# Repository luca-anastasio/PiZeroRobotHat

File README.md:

# PiZeroRobotHat
Raspberry Pi Zero Robot Hat

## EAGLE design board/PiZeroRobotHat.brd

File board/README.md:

## Pi Zero Robot Hat

### top

### bottom

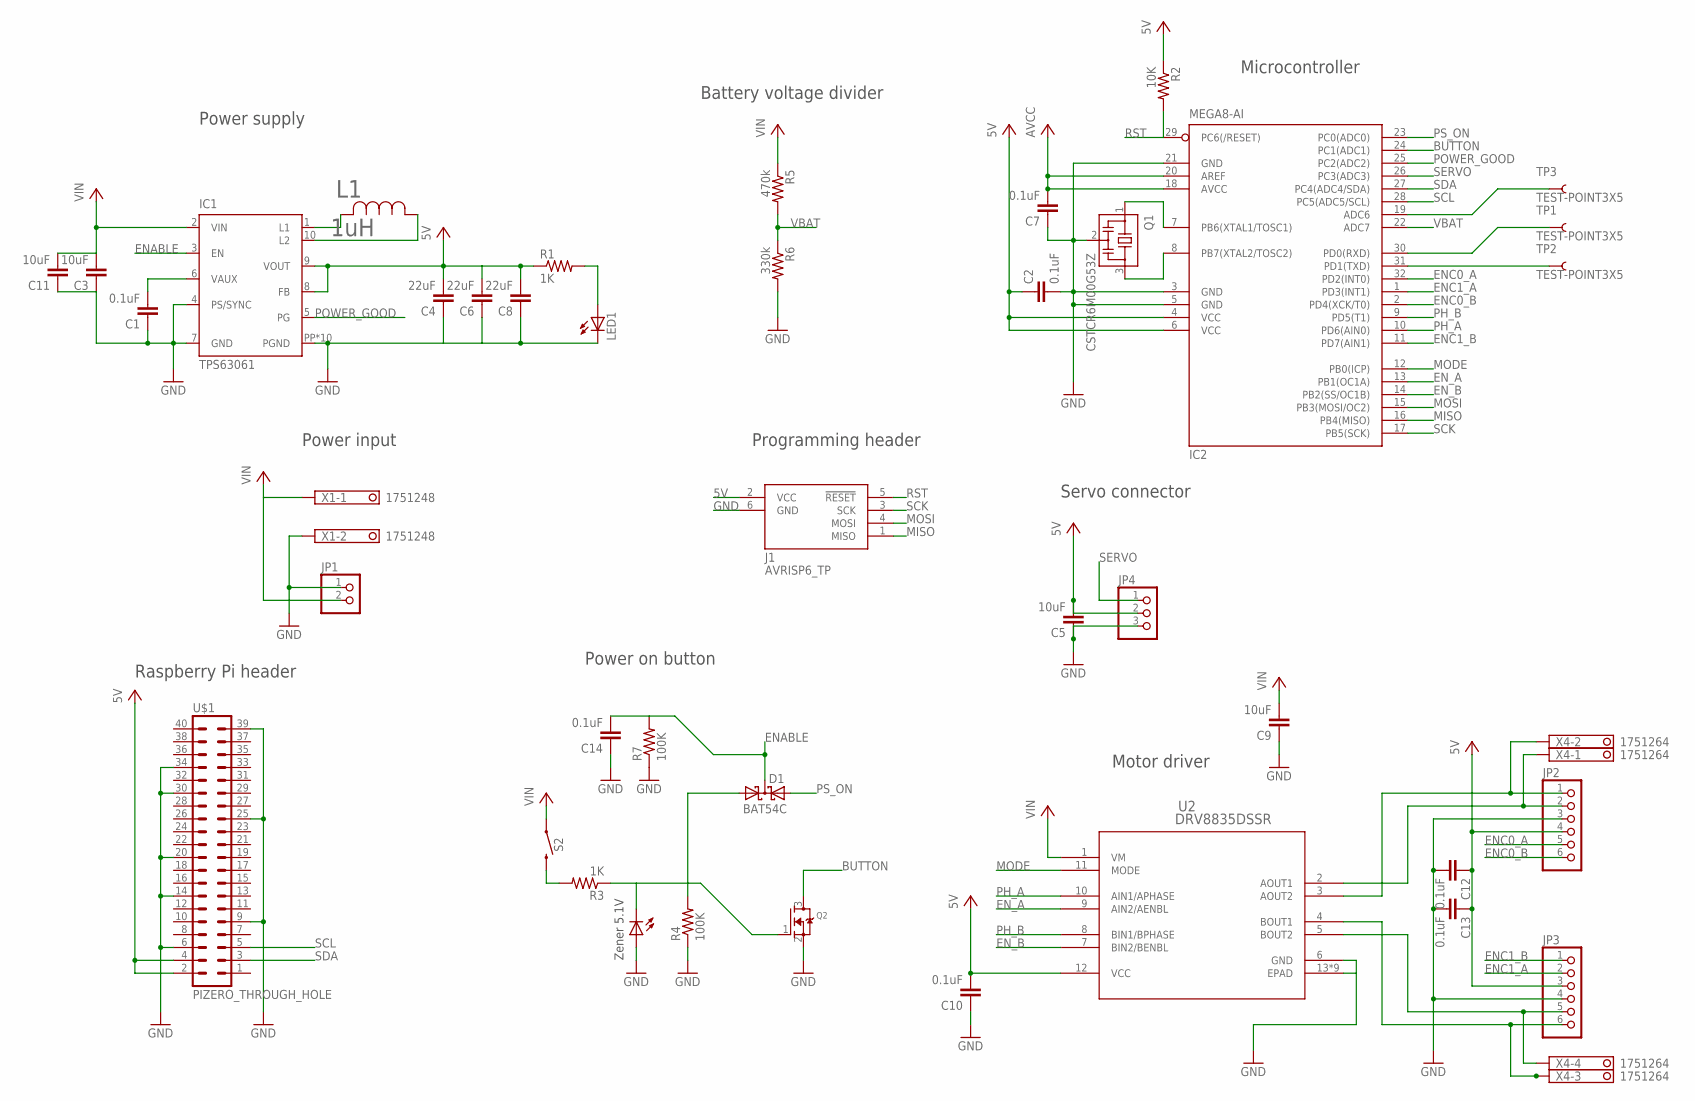
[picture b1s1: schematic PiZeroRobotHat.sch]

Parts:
C1, C2, C7, C10, C12, C13, C14: 0.1uF; C0603K
C3, C5, C9, C11: 10uF; C0805K
C4, C6, C8: 22uF; C0805K
D1: BAT54C; SOT23
IC1: TPS63061; DSC-S-PWSON-N10
IC2: MEGA8-AI; TQFP32-08
J1: AVRISP6_TP; 2X3_TP
JP1: PINHD-1X2; 1X02
JP2, JP3: PINHD-1X6; 1X06
JP4: PINHD-1X3; 1X03
L1: 1uH; IND_TAIYO_NR3015
LD1: PL006-WCR12; SOT23
LED1: LEDCHIPLED_0603; CHIPLED_0603
Q1: CSTCR6M00G53Z; CSTCR6M
Q2: MOSFET-NREFLOW; SOT23
R1, R3: 1K; R0603
R2: 10K; R0603
R4, R7: 100K; R0603
R5: 470k; R0603
R6: 330k; R0603
S2: MOMENTARY-SWITCH-SPST; TACTILE_SWITCH_SMD_4X3MM
TP1, TP2, TP3: TEST-POINT3X5; PAD.03X.05
U2: DRV8835DSSR; DSS12_P9X2
U$1: PIZERO_THROUGH_HOLE; PIZERO_THOUGH_HOLE
X1: 1751248
X4: 1751264

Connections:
0: IC2.30 (PD0(RXD)), TP1.P$1
1: IC2.31 (PD1(TXD)), TP2.P$1
5V: C2.1, C4.2, C5.2, C6.2, C7.2, C8.2, C10.2, C12.1, C13.1, IC1.8 (FB), IC1.9 (VOUT), IC2.4 (VCC), IC2.6 (VCC), IC2.18 (AVCC), IC2.20 (AREF), J1.2 (VCC), JP2.4, JP3.3, JP4.2, R1.1, R2.1, U2.12 (VCC), U$1.2, U$1.4
BT: D1.1 (A1), LD1.3 (C), Q2.1 (G), R3.1, R4.2
BUTTON: IC2.24 (PC1(ADC1)), Q2.3 (D)
ENABLE: C14.2, D1.3 (CC), IC1.3 (EN), R7.2
ENC0_A: IC2.32 (PD2(INT0)), JP2.5
ENC0_B: IC2.2 (PD4(XCK/T0)), JP2.6
ENC1_A: IC2.1 (PD3(INT1)), JP3.2
ENC1_B: IC2.11 (PD7(AIN1)), JP3.1
EN_A: IC2.13 (PB1(OC1A)), U2.9 (AIN2/AENBL)
EN_B: IC2.14 (PB2(SS/OC1B)), U2.7 (BIN2/BENBL)
GND: C1.1, C2.2, C3.1, C4.1, C5.1, C6.1, C7.1, C8.1, C9.1, C10.1, C11.1, C12.2, C13.2, C14.1, IC1.4 (PS/SYNC), IC1.7 (GND), IC1.PP (PGND), IC1.PP@1 (PGND), IC1.PP@2 (PGND), IC1.PP@3 (PGND), IC1.PP@4 (PGND), IC1.PP@5 (PGND), IC1.PP@7 (PGND), IC1.PP@8 (PGND), IC1.PP@9 (PGND), IC1.PP@10 (PGND), IC2.3 (GND), IC2.5 (GND), IC2.21 (GND), J1.6 (GND), JP1.1, JP2.3, JP3.4, JP4.3, LD1.1 (A), LED1.C, Q1.2, Q2.2 (S), R4.1, R6.2, R7.1, U2.6 (GND), U2.13 (EPAD), U2.14 (EPAD), U2.15 (EPAD), U2.16 (EPAD), U2.17 (EPAD), U2.18 (EPAD), U2.P$1 (EPAD), U2.P$2 (EPAD), U2.P$3 (EPAD), U$1.6, U$1.9, U$1.14, U$1.20, U$1.25, U$1.30, U$1.34, U$1.39, X1.2
LX1: IC1.1 (L1), L1.2
LX2: IC1.10 (L2), L1.1
M0A: JP2.1, U2.3 (AOUT2), X4.2
M0B: JP2.2, U2.2 (AOUT1), X4.1
M1A: JP3.6, U2.4 (BOUT1), X4.3
M1B: JP3.5, U2.5 (BOUT2), X4.4
MISO: IC2.16 (PB4(MISO)), J1.1 (MISO)
MODE: IC2.12 (PB0(ICP)), U2.11 (MODE)
MOSI: IC2.15 (PB3(MOSI/OC2)), J1.4 (MOSI)
unnamed: R3.2, S2.2
unnamed: LED1.A, R1.2
unnamed: C1.2, IC1.6 (VAUX)
unnamed: IC2.7 (PB6(XTAL1/TOSC1)), Q1.1
unnamed: IC2.8 (PB7(XTAL2/TOSC2)), Q1.3
unnamed: IC2.19 (ADC6), TP3.P$1
PH_A: IC2.10 (PD6(AIN0)), U2.10 (AIN1/APHASE)
PH_B: IC2.9 (PD5(T1)), U2.8 (BIN1/BPHASE)
POWER_GOOD: IC1.5 (PG), IC2.25 (PC2(ADC2))
PS_ON: D1.2 (A2), IC2.23 (PC0(ADC0))
RST: IC2.29 (PC6(/RESET)), J1.5 (!RESET), R2.2
SCK: IC2.17 (PB5(SCK)), J1.3 (SCK)
SCL: IC2.28 (PC5(ADC5/SCL)), U$1.5
SDA: IC2.27 (PC4(ADC4/SDA)), U$1.3
SERVO: IC2.26 (PC3(ADC3)), JP4.1
VBAT: IC2.22 (ADC7), R5.2, R6.1
VIN: C3.2, C9.2, C11.2, IC1.2 (VIN), JP1.2, R5.1, S2.1, U2.1 (VM), X1.1

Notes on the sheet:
Power supply
Zener 5.1V
Power input
Raspberry Pi header
Battery voltage divider
Microcontroller
Programming header
Servo connector
Motor driver
Power on button

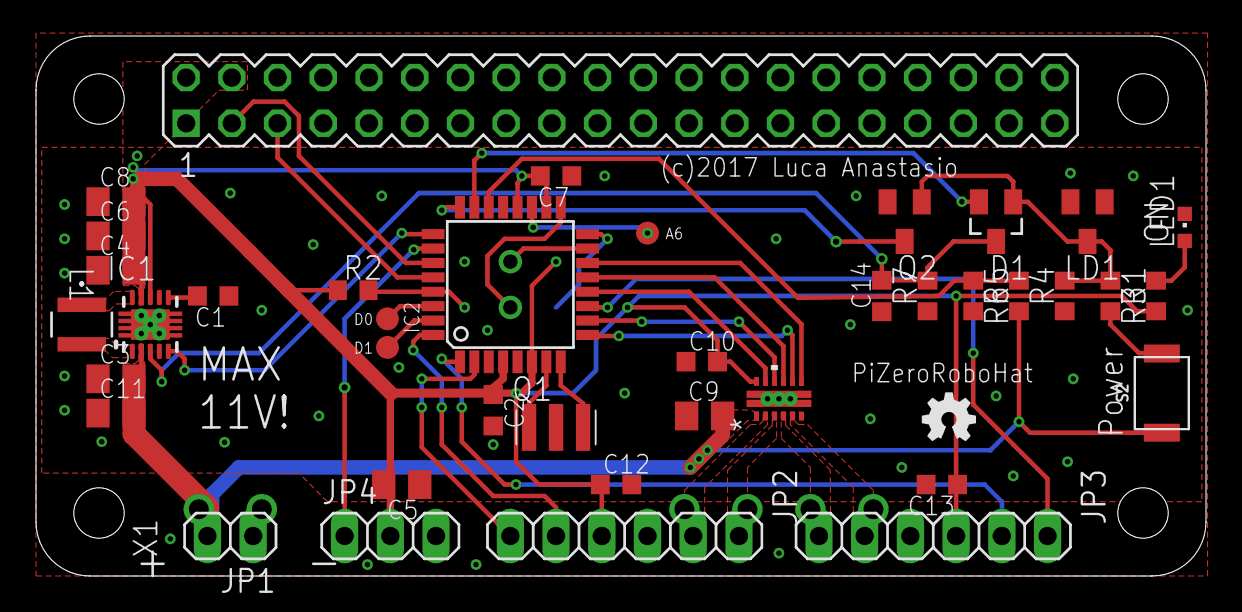
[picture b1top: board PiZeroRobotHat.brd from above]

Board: 2 copper layers, 65.0 x 30.0 mm, 42 parts (1 on the bottom side), 39 nets.

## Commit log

2017-08-19 first board
2017-08-29 board improvements
2017-12-23 board fixes

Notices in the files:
board/PiZeroRobotHat.brd:
(c)2017 Luca Anastasio
parts and their libraries:
SparkFun-Switches: Licensing: Creative Commons ShareAlike 4.0 International - https://creativecommons.org/licenses/by-sa/4.0
COPYRIGHT: Copyright C 2015 Accelerated Designs. All rights reserved
